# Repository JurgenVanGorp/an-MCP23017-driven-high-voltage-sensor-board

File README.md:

Guide creation date: 13-Nov-2021

# An MCP23017 driven high voltage sensor board
A schematic and hardware board for an MCP23017 multi-I/O controller driven 230V sensor board.

Previous topic: [Step 5: Building your hardware: an MCP23017 driven relay board.](https://github.com/JurgenVanGorp/an-mcp23017-driven-relay-board)

## Introduction

This guide describes a fairly straightforward way of measuring whether a light, motor, boiler ... has been switched on. The power is captured with a relay that switches the input of an MCP23017 to GND or +5V. The MCP23017 can the be read with a Raspberry Pi over the I2C bus. The solution is a PCB in Eurocard format (10cm x 16cm) with 15 high voltage (230V) relays, and one "Identification" LED output for verifying that the communication is working properly.

Let met start with answering your first question: "why are relays used, and not optocouplers?" Indeed, optocouplers have no moving parts and have a smaller footprint.

The answer is: power dissipation. The (230V) RT1 power relays that are used in this implementation consume 0,75 Watts each. When all 15 inputs are switched on, the board consumes 11.5 Watts, which is acceptable. Optocouplers typically switch on at 20...100 milliamps (TIL111: 100mA, 4N25/4N26/4N27/4N28: 60mA, PC817X series: min 20mA, typ. 50mA). Assuming we want to drive the optocoupler LED with 50mA, a 4.8KOhm series resistor is required (in practice: 4K7 or 5K1). The power consumption in the resistor would then be a whopping 12Watts. With all fifteen inputs switched on, you could easily boil an egg on the PCB.

So, using relays may seem "old school", but it does make sense.

The board needs a 12V power supply. The 12V is converted to 5V on the board, which is also used to power the mini secondary relays. With some modifications you can also use the board with 5V directly, but you would need to bridge the DC/DC converter. I am using 12V for the simple reason that all switches in my house operate on 12V. The translation to higher voltages is only done in the power box.

Four of the fifteen inputs will drive a secondary relay on the PCB. You can use these input sensors to directly drive (or disconnect) another device, e.g. an alarm or a warning light.

**WARNING** Even though the PCB board described below does provide you with physical segregation with relays, BE CAREFUL WITH THE HIGH VOLTAGES USED ON THE BOARD. The PCB design segregates the high voltage from the low voltage lines as much as possible, but won't protect you from accidently touching the back of the PCB. In the repository you can find the design of a cover that matches the PCB and that you can print for yourself with any 3D printer.

## Using and changing the files in this repository

I have created the schematic and PCB in this repository with the open and free [KiCad EDA](https://www.kicad.org/) software. I cannot express enough how much I am grateful to [the developers](https://www.kicad.org/about/kicad/) of this PCB software. As far as I'm concerned the times of too-expensive PCB software are over.

The PCB file looks as follows.

The GERBER PCB Files are included in the package, so you don't need to compile these for yourself.

There are many companies that will be able to create the PCB files for you. My personal favorite is [Eurocircuits.eu](https://www.eurocircuits.com/), but that's a personal choice of course. You can also create your own PCBs; the PDF file is added in the repository. But let's be honest, ordering the PCB looks a lot more professional and will last longer.

## Components used.

This is the list of components used, and where I have found them.

| Quantity | Component    | Value                     | Source                 | ~cost/Piece   |
|:--------:|--------------|--------------------------:|------------------------|--------------:|
| 1        | PCB Board    | See Gerber files | [eurocircuits.eu](https://www.eurocircuits.eu) | € 35.00 | 
| 9 | Resistor | 1K |  | € 0.10 | 
| 6 | Resistor | 1K |  | € 0.10 | 
| 2 | Resistor | 470 Ohm |  | € 0.10 | 
| 1        | Capacitor    | 22nF  | [conrad.com](https://www.conrad.com/p/tru-components-tc-k22nf5-ceramic-capacitor-tht-22-nf-100-v-20-1-pcs-1589451) | € 0.10 | 
| 5        | Capacitor    | 220nF | [conrad.com](https://www.conrad.com/p/kemet-c320c224m5u5ta-ceramic-capacitor-radial-lead-220-nf-50-v-20-l-x-w-x-h-508-x-318-x-584-mm-1-pcs-1420328) | € 0.60 | 
| 2        | Capacitor radial | 220uF | [conrad.com](https://www.conrad.com/p/europe-chemicon-eky-500ell221mj16s-electrolytic-capacitor-radial-lead-5-mm-220-f-50-v-20-x-h-10-mm-x-16-mm-1-pc-1505568) | € 0.50 | 
| 2 | Capacitor | 220uF axial | [conrad.com](https://www.conrad.com/p/vishay-2222-021-36221-electrolytic-capacitor-axial-lead-220-f-25-v-20-x-l-65-mm-x-18-mm-1-pcs-446056) | €1.60 | 
| 2 | Connector | RJ10 | [conrad.com](https://www.conrad.com/p/econ-connect-mjuse44gab-modular-mounted-socket-mjuse44gab-socket-horizontal-mount-number-of-pins-4-black-1-pcs-1311383) | € 0.60 | 
| 1        | Connector 1x2 | DG350-3.5-03P    | [conrad.com](https://www.conrad.com/p/degson-dg350-35-02p-14-00ah-200-screw-terminal-2-mm-number-of-pins-2-green-200-pcs-1595136) | | 7        | 1x6 Spring connector | PTR 54191060051E | [conrad.com](https://www.conrad.com/p/ptr-54191060051e-spring-loaded-terminal-075-mm-number-of-pins-6-pebble-grey-1-pcs-569770) | € 0.36 | 
| 3        | Jumper       | N/A      | e.g. [conrad.com](https://www.conrad.com/p/tru-components-shorting-jumper-contact-spacing-254-mm-pins-per-row2-content-100-pcs-1693950) | € 0.35 | 
| 15 | Relay | RT314730 | [conrad.com](https://www.conrad.be/p/te-connectivity-rt314730-printrelais-230-vac-16-a-1x-wisselcontact-1-stuks-504255) | € 6.22 | 
| 4 | Relay | G5V-1-5DC | [conrad.com](https://eu.mouser.com/ProductDetail/Omron/G5V-1-2-DC5?qs=sGAEpiMZZMsKEdP9slC0YbH1hXJZnuIH7AhUMezYhKg%3D) | € 1.45 | 
| 1        | IC           | MCP23017                  | [mouser.com](https://eu.mouser.com/ProductDetail/Microchip/MCP23017-E-SP?qs=sGAEpiMZZMsVgcksf1EMUq%252Bl%252ByrW%252Br2s)| € 1.35 |
| 2        | 14 pins socket | MCP23017                  | [mouser.com](https://www.conrad.com/p/tru-components-ic-socket-contact-spacing-254-mm-762-mm-number-of-pins-14-1-pcs-1568704) | € 0.40 |
| 1        | LED "IDENT"  | Green 5 mm | [conrad.com](https://www.conrad.com/p/vishay-tlhr-5400-led-wired-super-red-circular-5-mm-10-mcd-30-30-ma-2-v-184389) | € 0.20 | 
| 1        | LED "POWER"  | Red 5 mm | [conrad.com](https://www.conrad.com/p/kingbright-l-7113id-led-wired-red-circular-5-mm-45-mcd-30-20-ma-2-v-180139) | € 0.20 | 
| 1        | 12V to 5V DC | OKI-78SR-5_1.5-W36H-C **(1)** | [mouser.com](https://eu.mouser.com/ProductDetail/Murata/OKI-78SR-5-15-W36H-C?qs=sGAEpiMZZMsbRVlHDoeFZD%252BySXGErvIJc3su7QBo1Is%3D) | € 3.64 | 
| 4       | Diode        | 1N4007 | [conrad.com](https://www.conrad.com/p/diotec-si-rectifier-1n4007-do-204al-1000-v-1-a-162272) | € 0.09 | 
| TOTAL   | | | | ~ € 153 |

**(1)** The OKI-78SR is a 12V DC to 5V DC converter. It is pin-compatible with an [LM7805](https://eu.mouser.com/ProductDetail/Texas-Instruments/LM7805CT?qs=sGAEpiMZZMsFKQfwwdJx%2FxW4Tr%252BxPyoqmeSSFfZw3i4%3D). The current drawn is very low, so feel free to replace it with an LM7805 if you prefer.

The assembled board should look something like the following. The RJ10 connectors may be hard to find, so you may want to solder the wires directly.

## Protective Cover

The high voltage lines are routed on the PCB such that they are at a distance from the low-voltage lines. However, it is still possible to touch the high voltage pins at the bottom of the PCB. In the "Protection Shield" folder the gcode and stl files can be found to print a protective cover for the PCB. The holes match the holes in the PCB.

The 3D layout was created with an older version of [Sketchup](https://www.sketchup.com/plans-and-pricing/sketchup-free). The original file is added in the repository.

## Schematic decription

The overall schematic looks as follows. You can [download the shematic in PDF format here](https://github.com/JurgenVanGorp/an-MCP23017-driven-high-voltage-sensor-board/blob/main/PCB%20MCP23017%20High%20Voltage%20sensors/Schematic.pdf).

This overview is a bit crowded, and not easy to follow. Let's highlight a few details here. 

In the top left and top right of the schematic, you can find the connector blocks. The connectors on the right hand are the 230V inputs. The 2 x 15 inputs are paired and directly drive the 230V relays.

The connection is straightforward. If a relay is not powered, the MCP23017 pin is connected to GND. If the relay is powered, the pin is connected to +5V.

The connector block on the top left side are secondary relays connected to the GPA0..GPA3 inputs. The NO (Normally Open), NC (Normally Connected) and CO (Common) pins of the relays are routed to the connectors.

Here also, the connection is straightforward. The 230V relay not only connects GND or +5V to the MCP23017 pin, but also powers a secondary relay. A diode is placed over the secondary relay to protect the PCB from over-voltage glitches when the relay is switched off.

Finally, let's look at the MCP23017 block in more detail.
* The input pins of both GPA and GPB are routed to the relay blocks. Each input is protected with a 1KOhm resistor to protect the pin in case the MCP23017 pin is accidently configured as an output.
* GPB7 ("pin 15" in Home Assistant) is connected to the "Identification" LED D6 and can be used to identify the board and test the MCP23017 operation.
* The RJ10 connectors J4 and J10 are used to connect the I2C pins to the Raspberry Pi. Remark that both connectors are configured fully parallel, so that the connectors can be used to cascade multiple boards. 
* Jumpers JP1 .. JP3 are used as the address selectors.
* LED D1 is just connected to the +5V output and can be used to verify the +5V power.

## Mounting the PCB Board

The PCBs are 10cm x 16cm which allows mounting them in a standard EuroRack, as in the image below. If you want to know more about Euroracks, [RS gives a nice overview here](https://nl.rs-online.com/web/generalDisplay.html?id=ideas-and-advice/eurocards-pcb-guide). They also sell different types of enclosures.

An alternate way for mounting the board, is a DIN rail case. The components for a DIN rail mount are e.g. the following.

| Quantity | Component                    | Description            | Source                 | ~cost/Piece   |
|:--------:|------------------------------|------------------------|------------------------|--------------:|
| 2 or 3   | Phoenix Contact UM108-FE     | DIN rail mount         | [conrad.com](https://www.conrad.com/p/phoenix-contact-um108-fe-din-rail-casing-base-1075-plastic-10-pcs-454634) | € 0.70 | 
| 1        | Phoenix Contact UM108-SEFE/R | Right side panel       | [conrad.com](https://www.conrad.com/p/phoenix-contact-um108-sefer-din-rail-casing-side-panel-plastic-10-pcs-453303) | € 1.00 |
| 1        | Phoenix Contact UM108-SEFE/R | Left side panel        | [conrad.com](https://www.conrad.com/search?search=459039&searchType=regular) | € 1.00 |
| 1        | Phoenix Contact UM100-PROFIL 100CM | back plate (1m)  | [conrad.com](https://www.conrad.com/p/phoenix-contact-um100-profil-100cm-din-rail-casing-plastic-1-pcs-456207) | € 30.00 |

Next topic: [An example Home Assistant Installation setup](https://github.com/JurgenVanGorp/an-MCP23017-driven-high-voltage-sensor-board)

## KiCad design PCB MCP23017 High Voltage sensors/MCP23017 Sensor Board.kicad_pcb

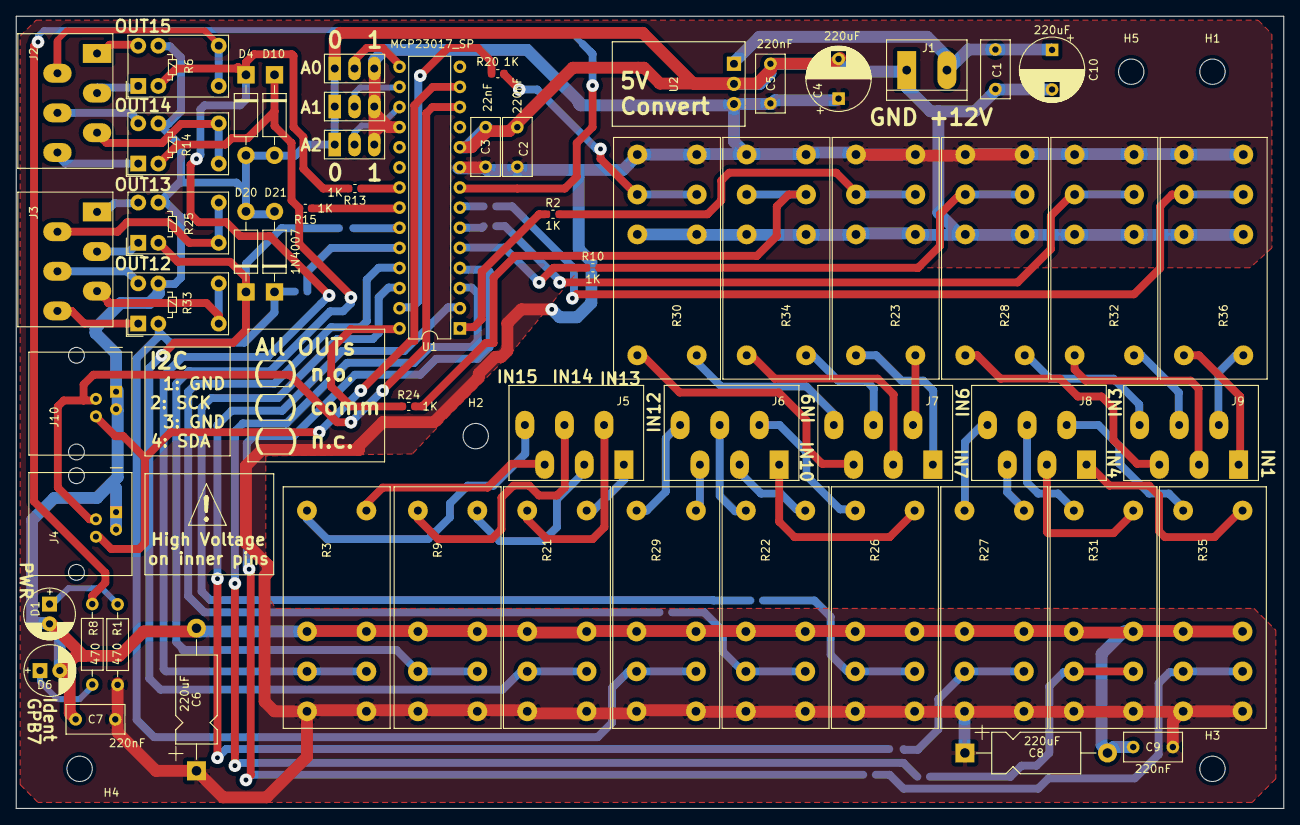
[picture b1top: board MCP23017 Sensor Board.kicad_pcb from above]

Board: 2 copper layers, 160.0 x 100.0 mm, 72 parts (0 on the bottom side), 83 nets.

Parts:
C1, C2, C5, C7, C9: 220nF; C_Rect_L7.2mm_W3.5mm_P5.00mm_FKS2_FKP2_MKS2_MKP2
C3: 22nF; C_Rect_L7.2mm_W3.5mm_P5.00mm_FKS2_FKP2_MKS2_MKP2
C4, C10: 220uF; CP_Radial_D8.0mm_P5.00mm
C6, C8: 220uF; CP_Axial_L11.0mm_D5.0mm_P18.00mm_Horizontal
D1: LED Red; LED_Radial_D6.3mm_P2.50mm_Jurgen
D4, D10, D20, D21: 1N4007; D_DO-41_SOD81_P10.16mm_Horizontal
D6: LED Green; LED_Radial_D6.3mm_P2.50mm_Jurgen
H1, H2, H3, H4, H5: M3 MountingHole; MountingHole_3.2mm_M3
J1: Vin12V; TerminalBlock_bornier-2_P5.08mm_jurgen
J2, J3, J5, J6, J7, J8, J9: Screw_Terminal_01x06; Connector_1x6_ZigZag
J4, J10: RJ10; RJ11
JP1, JP2, JP3: Jumper_NC_Dual; Connector_1x3_Normal
R1, R8: 470; R_Axial_DIN0207_L6.3mm_D2.5mm_P10.16mm_Horizontal
R2, R10, R13, R15, R20, R24: 1K; R_0603_1608Metric
R3, R9, R21, R22, R23, R26, R27, R28, R29, R30, R31, R32, R34, R35, R36: RT314730; Relay_230V
R4, R5, R7, R11, R12, R16, R17, R18, R19: 1K; R_0603_1608Metric_Bottom
R6, R14, R25, R33: G5V-1; Relay_SPDT_Omron_G5V-1
U1: MCP23017_SP; DIP-28_W7.62mm
U2: OKI-78SR-5_1.5-W36H-C; Converter_DCDC_muRata_OKI-78SR_Horizontal

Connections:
/GPA0: D4.1, R3.11, R6.2, R13.2
/GPA1: D10.1, R9.11, R14.2, R15.2
/GPA2: D20.1, R16.2, R21.11, R25.2
/GPA3: D21.1, R17.2, R29.11, R33.2
/GPA4: R18.2, R22.11
/GPA5: R19.2, R26.11
/GPA6: R20.2, R30.11
/GPA7: R24.2, R34.11
/GPB0: R2.2, R23.11
/GPB1: R4.2, R27.11
/GPB2: R5.2, R31.11
/GPB3: R7.2, R35.11
/GPB4: R10.2, R28.11
/GPB5: R11.2, R32.11
/GPB6: R12.2, R36.11
/ReAa0: J5.6, R3.A2
/ReAa1: J5.4, R9.A2
/ReAa2: J5.2, R21.A2
/ReAa3: J6.6, R29.A2
/ReAa4: J6.4, R22.A2
/ReAa5: J6.2, R26.A2
/ReAa6: J7.6, R30.A2
/ReAa7: J7.4, R34.A2
/ReAb0: J5.5, R3.A1
/ReAb1: J5.3, R9.A1
/ReAb2: J5.1, R21.A1
/ReAb3: J6.5, R29.A1
/ReAb4: J6.3, R22.A1
/ReAb5: J6.1, R26.A1
/ReAb6: J7.5, R30.A1
/ReAb7: J7.3, R34.A1
/ReBa0: J7.2, R23.A2
/ReBa1: J8.6, R27.A2
/ReBa2: J8.4, R31.A2
/ReBa3: J8.2, R35.A2
/ReBa4: J9.6, R28.A2
/ReBa5: J9.4, R32.A2
/ReBa6: J9.2, R36.A2
/ReBb0: J7.1, R23.A1
/ReBb1: J8.5, R27.A1
/ReBb2: J8.3, R31.A1
/ReBb3: J8.1, R35.A1
/ReBb4: J9.5, R28.A1
/ReBb5: J9.3, R32.A1
/ReBb6: J9.1, R36.A1
/SecCO1: J2.2, R6.5, R6.6
/SecCO2: J2.5, R14.5, R14.6
/SecCO3: J3.2, R25.5, R25.6
/SecCO4: J3.5, R33.5, R33.6
/SecNC1: J2.3, R6.1
/SecNC2: J2.6, R14.1
/SecNC3: J3.3, R25.1
/SecNC4: J3.6, R33.1
/SecNO1: J2.1, R6.10
/SecNO2: J2.4, R14.10
/SecNO3: J3.1, R25.10
/SecNO4: J3.4, R33.10
GND: C1.2, C2.2, C3.2, C4.2, C5.2, C6.2, C7.2, C8.2, C9.2, C10.2, D1.1, D4.2, D6.1, D10.2, D20.2, D21.2, J1.1, J4.1, J4.3, J10.1, J10.3, JP1.1, JP2.1, JP3.1, R3.12, R6.9, R9.12, R14.9, R21.12, R22.12, R23.12, R25.9, R26.12, R27.12, R28.12, R29.12, R30.12, R31.12, R32.12, R33.9, R34.12, R35.12, R36.12, U1.10, U2.2
unnamed: C1.1, C10.1, J1.2, U2.1
unnamed: D1.2, R1.2
unnamed: D6.2, R8.2
unnamed: J4.2, J10.2, U1.12
unnamed: J4.4, J10.4, U1.13
unnamed: JP1.2, U1.17
unnamed: JP2.2, U1.16
unnamed: JP3.2, U1.15
unnamed: R2.1, U1.1
unnamed: R4.1, U1.2
unnamed: R5.1, U1.3
unnamed: R7.1, U1.4
unnamed: R8.1, U1.8
unnamed: R10.1, U1.5
unnamed: R11.1, U1.6
unnamed: R12.1, U1.7
unnamed: R13.1, U1.21
unnamed: R15.1, U1.22
unnamed: R16.1, U1.23
unnamed: R17.1, U1.24
unnamed: R18.1, U1.25
unnamed: R19.1, U1.26
unnamed: R20.1, U1.27
unnamed: R24.1, U1.28
VCC: C2.1, C3.1, C4.1, C5.1, C6.1, C7.1, C8.1, C9.1, JP1.3, JP2.3, JP3.3, R1.1, R3.14, R9.14, R21.14, R22.14, R23.14, R26.14, R27.14, R28.14, R29.14, R30.14, R31.14, R32.14, R34.14, R35.14, R36.14, U1.9, U1.18, U2.3

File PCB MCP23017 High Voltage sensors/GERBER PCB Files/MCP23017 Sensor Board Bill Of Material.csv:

"Id";"Designator";"Package";"Quantity";"Designation";"Supplier and ref";
1;"R16,R17,R12,R18,R7,R19,R11,R4,R5";"R_0603_1608Metric_Bottom";9;"1K";;;
2;"R13,R2,R24,R20,R15,R10";"R_0603_1608Metric";6;"1K";;;
3;"H5,H4,H3,H2,H1";"MountingHole_3.2mm_M3";5;"M3 MountingHole";;;
4;"C10,C4";"CP_Radial_D8.0mm_P5.00mm";2;"220uF";;;
5;"C9,C7,C2,C5,C1";"C_Rect_L7.2mm_W3.5mm_P5.00mm_FKS2_FKP2_MKS2_MKP2";5;"220nF";;;
6;"C8,C6";"CP_Axial_L11.0mm_D5.0mm_P18.00mm_Horizontal";2;"220uF";;;
7;"C3";"C_Rect_L7.2mm_W3.5mm_P5.00mm_FKS2_FKP2_MKS2_MKP2";1;"22nF";;;
8;"J10,J4";"RJ11";2;"RJ10";;;
9;"R3,R9,R36,R35,R34,R32,R31,R30,R28,R27,R26,R22,R29,R23,R21";"Relay_230V";15;"RT314730";;;
10;"U1";"DIP-28_W7.62mm";1;"MCP23017_SP";;;
11;"R8,R1";"R_Axial_DIN0207_L6.3mm_D2.5mm_P10.16mm_Horizontal";2;"470";;;
12;"D6";"LED_Radial_D6.3mm_P2.50mm_Jurgen";1;"LED Green";;;
13;"D1";"LED_Radial_D6.3mm_P2.50mm_Jurgen";1;"LED Red";;;
14;"JP1,JP3,JP2";"Connector_1x3_Normal";3;"Jumper_NC_Dual";;;
15;"U2";"Converter_DCDC_muRata_OKI-78SR_Horizontal";1;"OKI-78SR-5_1.5-W36H-C";;;
16;"J1";"TerminalBlock_bornier-2_P5.08mm_jurgen";1;"Vin12V";;;
17;"J9,J8,J7,J6,J3,J2,J5";"Connector_1x6_ZigZag";7;"Screw_Terminal_01x06";;;
18;"R33,R14,R25,R6";"Relay_SPDT_Omron_G5V-1";4;"G5V-1";;;
19;"D21,D10,D20,D4";"D_DO-41_SOD81_P10.16mm_Horizontal";4;"1N4007";;;

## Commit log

2021-11-14 PCB layouts and protection shield
2021-11-14 PCB Images
2021-11-15 Detailed description
